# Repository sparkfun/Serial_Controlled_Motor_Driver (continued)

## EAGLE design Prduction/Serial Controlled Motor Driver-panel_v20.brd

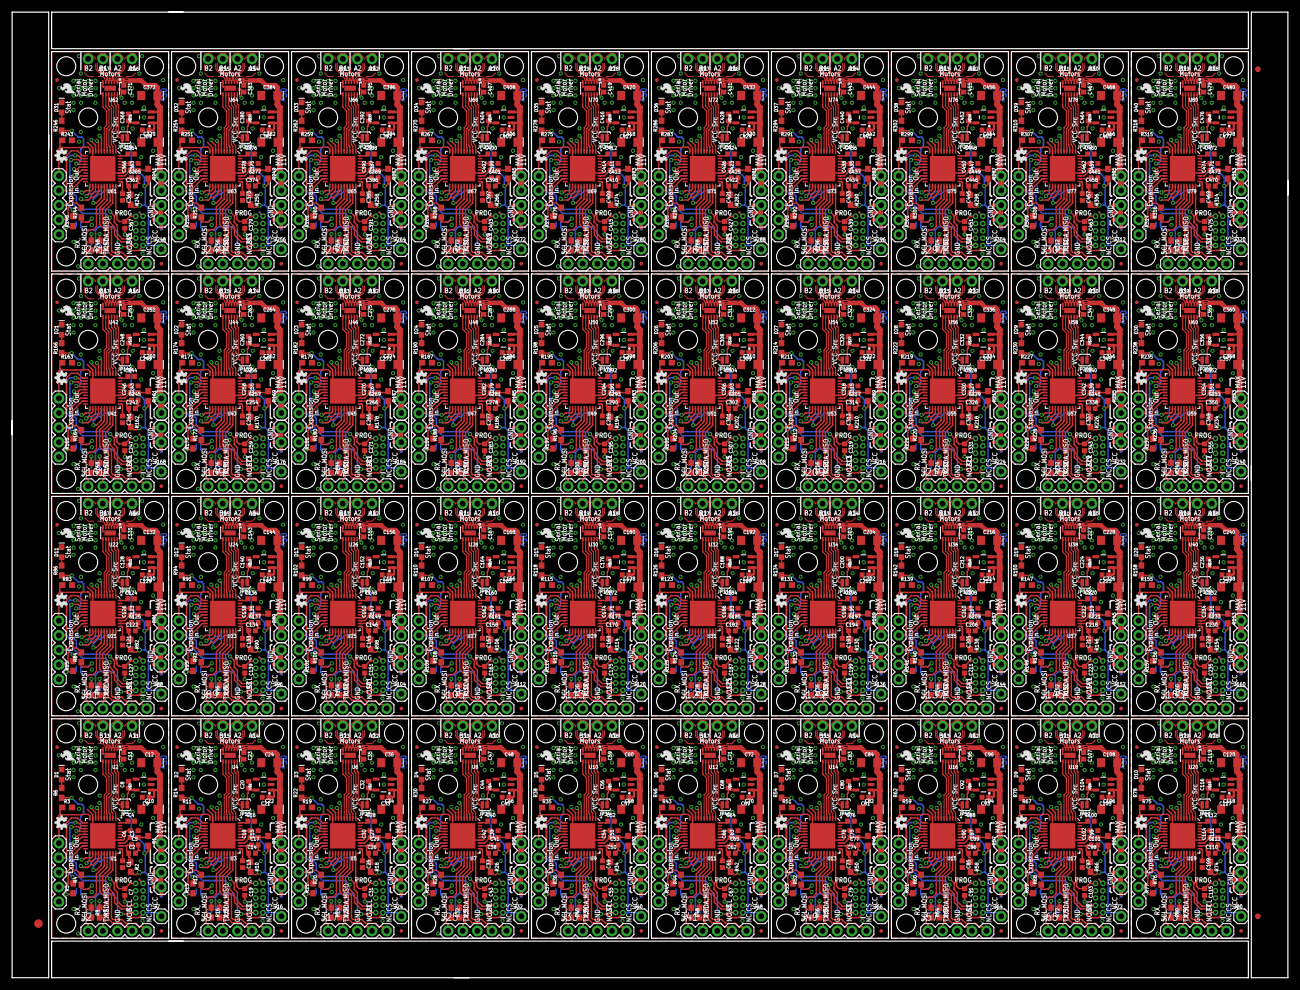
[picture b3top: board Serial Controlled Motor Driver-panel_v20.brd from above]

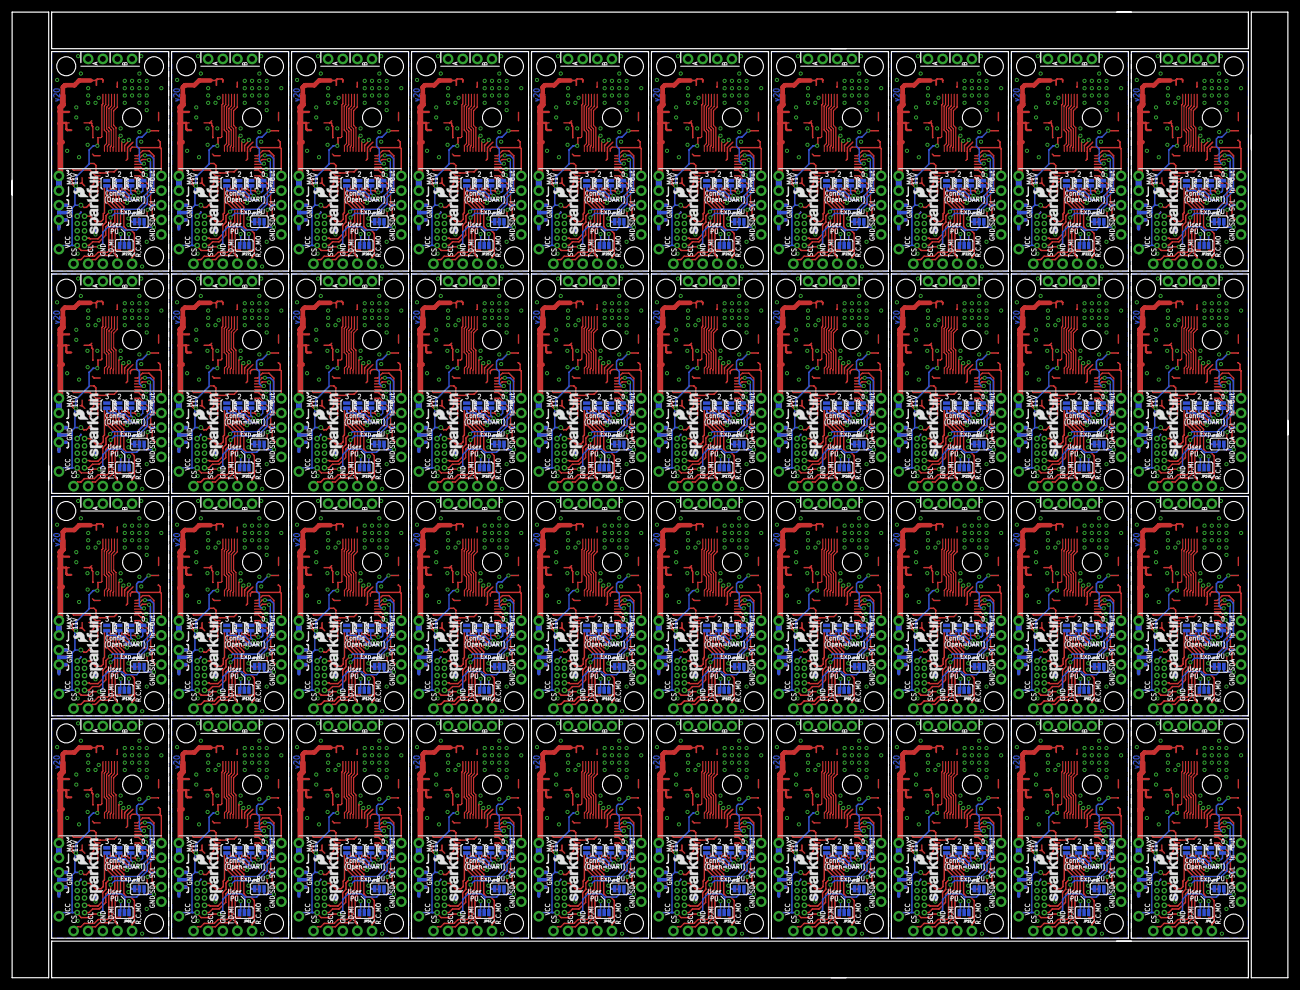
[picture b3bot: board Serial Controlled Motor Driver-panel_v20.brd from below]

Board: 2 copper layers, 221.5 x 167.6 mm, 1923 parts (280 on the bottom side), 1520 nets.

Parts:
C1, C2, C3, C4, C8, C9, C13, C14, C15, C16, C20, C21, C25, C26, C27, C28, C32, C33, C37, C38, C39, C40, C44, C45, C49, C50, C51, C52, C56, C57, C61, C62, C63, C64, C68, C69, C73, C74, C75, C76, C80, C81, C85, C86, C87, C88, C92, C93, C97, C98, C99, C100, C104, C105, C109, C110, C111, C112, C116, C117, C121, C122, C123, C124, C128, C129, C133, C134, C135, C136, C140, C141, C145, C146, C147, C148, C152, C153, C157, C158, C159, C160, C164, C165, C169, C170, C171, C172, C176, C177, C181, C182, C183, C184, C188, C189, C193, C194, C195, C196, C200, C201, C205, C206, C207, C208, C212, C213, C217, C218, C219, C220, C224, C225, C229, C230, C231, C232, C236, C237, C241, C242, C243, C244, C248, C249, C253, C254, C255, C256, C260, C261, C265, C266, C267, C268, C272, C273, C277, C278, C279, C280, C284, C285, C289, C290, C291, C292, C296, C297, C301, C302, C303, C304, C308, C309, C313, C314, C315, C316, C320, C321, C325, C326, C327, C328, C332, C333, C337, C338, C339, C340, C344, C345, C349, C350, C351, C352, C356, C357, C361, C362, C363, C364, C368, C369, C373, C374, C375, C376, C380, C381, C385, C386, C387, C388, C392, C393, C397, C398, C399, C400, C404, C405, C409, C410, C411, C412, C416, C417, C421, C422, C423, C424, C428, C429, C433, C434, C435, C436, C440, C441, C445, C446, C447, C448, C452, C453, C457, C458, C459, C460, C464, C465, C469, C470, C471, C472, C476, C477: 1.0uF; 0402
C5, C6, C7, C11, C17, C18, C19, C23, C29, C30, C31, C35, C41, C42, C43, C47, C53, C54, C55, C59, C65, C66, C67, C71, C77, C78, C79, C83, C89, C90, C91, C95, C101, C102, C103, C107, C113, C114, C115, C119, C125, C126, C127, C131, C137, C138, C139, C143, C149, C150, C151, C155, C161, C162, C163, C167, C173, C174, C175, C179, C185, C186, C187, C191, C197, C198, C199, C203, C209, C210, C211, C215, C221, C222, C223, C227, C233, C234, C235, C239, C245, C246, C247, C251, C257, C258, C259, C263, C269, C270, C271, C275, C281, C282, C283, C287, C293, C294, C295, C299, C305, C306, C307, C311, C317, C318, C319, C323, C329, C330, C331, C335, C341, C342, C343, C347, C353, C354, C355, C359, C365, C366, C367, C371, C377, C378, C379, C383, C389, C390, C391, C395, C401, C402, C403, C407, C413, C414, C415, C419, C425, C426, C427, C431, C437, C438, C439, C443, C449, C450, C451, C455, C461, C462, C463, C467, C473, C474, C475, C479: 0.1uF; 0402
C10, C12, C22, C24, C34, C36, C46, C48, C58, C60, C70, C72, C82, C84, C94, C96, C106, C108, C118, C120, C130, C132, C142, C144, C154, C156, C166, C168, C178, C180, C190, C192, C202, C204, C214, C216, C226, C228, C238, C240, C250, C252, C262, C264, C274, C276, C286, C288, C298, C300, C310, C312, C322, C324, C334, C336, C346, C348, C358, C360, C370, C372, C382, C384, C394, C396, C406, C408, C418, C420, C430, C432, C442, C444, C454, C456, C466, C468, C478, C480: 10uF; EIA3216
D1, D2, D3, D4, D5, D6, D7, D8, D9, D10, D11, D12, D13, D14, D15, D16, D17, D18, D19, D20, D21, D22, D23, D24, D25, D26, D27, D28, D29, D30, D31, D32, D33, D34, D35, D36, D37, D38, D39, D40: RED; LED-0603
E$1: FIDUCIAL-1.5X3
E$5, E$6: FIDUCIAL-1X2
FD1, FD2, FD3, FD4, FD5, FD6, FD7, FD8, FD9, FD10, FD11, FD12, FD13, FD14, FD15, FD16, FD17, FD18, FD19, FD20, FD21, FD22, FD23, FD24, FD25, FD26, FD27, FD28, FD29, FD30, FD31, FD32, FD33, FD34, FD35, FD36, FD37, FD38, FD39, FD40, FD41, FD42, FD43, FD44, FD45, FD46, FD47, FD48, FD49, FD50, FD51, FD52, FD53, FD54, FD55, FD56, FD57, FD58, FD59, FD60, FD61, FD62, FD63, FD64, FD65, FD66, FD67, FD68, FD69, FD70, FD71, FD72, FD73, FD74, FD75, FD76, FD77, FD78, FD79, FD80: FIDUCIALUFIDUCIAL; MICRO-FIDUCIAL
H1, H2, H3, H4, H5, H6, H7, H8, H9, H10, H11, H12, H13, H14, H15, H16, H17, H18, H19, H20, H21, H22, H23, H24, H25, H26, H27, H28, H29, H30, H31, H32, H33, H34, H35, H36, H37, H38, H39, H40, H41, H42, H43, H44, H45, H46, H47, H48, H49, H50, H51, H52, H53, H54, H55, H56, H57, H58, H59, H60, H61, H62, H63, H64, H65, H66, H67, H68, H69, H70, H71, H72, H73, H74, H75, H76, H77, H78, H79, H80, H81, H82, H83, H84, H85, H86, H87, H88, H89, H90, H91, H92, H93, H94, H95, H96, H97, H98, H99, H100, H101, H102, H103, H104, H105, H106, H107, H108, H109, H110, H111, H112, H113, H114, H115, H116, H117, H118, H119, H120, H121, H122, H123, H124, H125, H126, H127, H128, H129, H130, H131, H132, H133, H134, H135, H136, H137, H138, H139, H140, H141, H142, H143, H144, H145, H146, H147, H148, H149, H150, H151, H152, H153, H154, H155, H156, H157, H158, H159, H160: STAND-OFF
J1, J3, J14, J15, J22, J23, J30, J31, J38, J39, J46, J47, J54, J55, J62, J63, J70, J71, J78, J79, J86, J87, J94, J95, J102, J103, J110, J111, J118, J119, J126, J127, J134, J135, J142, J143, J150, J151, J158, J159, J166, J167, J174, J175, J182, J183, J190, J191, J198, J199, J206, J207, J214, J215, J222, J223, J230, J231, J238, J239, J246, J247, J254, J255, J262, J263, J270, J271, J278, J279, J286, J287, J294, J295, J302, J303, J310, J311, J318, J319: DNP; 1X02_NO_SILK
J2, J4, J9, J10, J17, J18, J25, J26, J33, J34, J41, J42, J49, J50, J57, J58, J65, J66, J73, J74, J81, J82, J89, J90, J97, J98, J105, J106, J113, J114, J121, J122, J129, J130, J137, J138, J145, J146, J153, J154, J161, J162, J169, J170, J177, J178, J185, J186, J193, J194, J201, J202, J209, J210, J217, J218, J225, J226, J233, J234, J241, J242, J249, J250, J257, J258, J265, J266, J273, J274, J281, J282, J289, J290, J297, J298, J305, J306, J313, J314: DNP; 1X05
J5, J6, J11, J12, J19, J20, J27, J28, J35, J36, J43, J44, J51, J52, J59, J60, J67, J68, J75, J76, J83, J84, J91, J92, J99, J100, J107, J108, J115, J116, J123, J124, J131, J132, J139, J140, J147, J148, J155, J156, J163, J164, J171, J172, J179, J180, J187, J188, J195, J196, J203, J204, J211, J212, J219, J220, J227, J228, J235, J236, J243, J244, J251, J252, J259, J260, J267, J268, J275, J276, J283, J284, J291, J292, J299, J300, J307, J308, J315, J316: DNP; 1X02@1
J7, J16, J24, J32, J40, J48, J56, J64, J72, J80, J88, J96, J104, J112, J120, J128, J136, J144, J152, J160, J168, J176, J184, J192, J200, J208, J216, J224, J232, J240, J248, J256, J264, J272, J280, J288, J296, J304, J312, J320: DNP; 1X01
J8, J13, J21, J29, J37, J45, J53, J61, J69, J77, J85, J93, J101, J109, J117, J125, J133, J141, J149, J157, J165, J173, J181, J189, J197, J205, J213, J221, J229, J237, J245, J253, J261, J269, J277, J285, J293, J301, J309, J317: CORTEX_DEBUGPTH; 2X5-PTH-1.27MM
JP1, JP2, JP3, JP4, JP8, JP9, JP10, JP11, JP15, JP16, JP17, JP18, JP22, JP23, JP24, JP25, JP29, JP30, JP31, JP32, JP36, JP37, JP38, JP39, JP43, JP44, JP45, JP46, JP50, JP51, JP52, JP53, JP57, JP58, JP59, JP60, JP64, JP65, JP66, JP67, JP71, JP72, JP73, JP74, JP78, JP79, JP80, JP81, JP85, JP86, JP87, JP88, JP92, JP93, JP94, JP95, JP99, JP100, JP101, JP102, JP106, JP107, JP108, JP109, JP113, JP114, JP115, JP116, JP120, JP121, JP122, JP123, JP127, JP128, JP129, JP130, JP134, JP135, JP136, JP137, JP141, JP142, JP143, JP144, JP148, JP149, JP150, JP151, JP155, JP156, JP157, JP158, JP162, JP163, JP164, JP165, JP169, JP170, JP171, JP172, JP176, JP177, JP178, JP179, JP183, JP184, JP185, JP186, JP190, JP191, JP192, JP193, JP197, JP198, JP199, JP200, JP204, JP205, JP206, JP207, JP211, JP212, JP213, JP214, JP218, JP219, JP220, JP221, JP225, JP226, JP227, JP228, JP232, JP233, JP234, JP235, JP239, JP240, JP241, JP242, JP246, JP247, JP248, JP249, JP253, JP254, JP255, JP256, JP260, JP261, JP262, JP263, JP267, JP268, JP269, JP270, JP274, JP275, JP276, JP277: JUMPER-PAD-2; PAD-JUMPER-2-NO_YES_SILK
JP5, JP13, JP20, JP27, JP34, JP41, JP48, JP55, JP62, JP69, JP76, JP83, JP90, JP97, JP104, JP111, JP118, JP125, JP132, JP139, JP146, JP153, JP160, JP167, JP174, JP181, JP188, JP195, JP202, JP209, JP216, JP223, JP230, JP237, JP244, JP251, JP258, JP265, JP272, JP279: JUMPER-PAD-2; PAD-JUMPER-2-NC_BY_PASTE_YES_SILK
JP6, JP7, JP12, JP14, JP19, JP21, JP26, JP28, JP33, JP35, JP40, JP42, JP47, JP49, JP54, JP56, JP61, JP63, JP68, JP70, JP75, JP77, JP82, JP84, JP89, JP91, JP96, JP98, JP103, JP105, JP110, JP112, JP117, JP119, JP124, JP126, JP131, JP133, JP138, JP140, JP145, JP147, JP152, JP154, JP159, JP161, JP166, JP168, JP173, JP175, JP180, JP182, JP187, JP189, JP194, JP196, JP201, JP203, JP208, JP210, JP215, JP217, JP222, JP224, JP229, JP231, JP236, JP238, JP243, JP245, JP250, JP252, JP257, JP259, JP264, JP266, JP271, JP273, JP278, JP280: JUMPER-PAD-3-NOYES_SILK; PAD-JUMPER-3-NO_YES_SILK
LOGO1, LOGO4, LOGO7, LOGO10, LOGO13, LOGO16, LOGO19, LOGO22, LOGO25, LOGO28, LOGO31, LOGO34, LOGO37, LOGO40, LOGO43, LOGO46, LOGO49, LOGO52, LOGO55, LOGO58, LOGO61, LOGO64, LOGO67, LOGO70, LOGO73, LOGO76, LOGO79, LOGO82, LOGO85, LOGO88, LOGO91, LOGO94, LOGO97, LOGO100, LOGO103, LOGO106, LOGO109, LOGO112, LOGO115, LOGO118: SFE_LOGO_FLAME.1_INCH; SFE_LOGO_FLAME_.1
LOGO2, LOGO5, LOGO8, LOGO11, LOGO14, LOGO17, LOGO20, LOGO23, LOGO26, LOGO29, LOGO32, LOGO35, LOGO38, LOGO41, LOGO44, LOGO47, LOGO50, LOGO53, LOGO56, LOGO59, LOGO62, LOGO65, LOGO68, LOGO71, LOGO74, LOGO77, LOGO80, LOGO83, LOGO86, LOGO89, LOGO92, LOGO95, LOGO98, LOGO101, LOGO104, LOGO107, LOGO110, LOGO113, LOGO116, LOGO119: OSHW-LOGOMINI; OSHW-LOGO-MINI
LOGO3, LOGO6, LOGO9, LOGO12, LOGO15, LOGO18, LOGO21, LOGO24, LOGO27, LOGO30, LOGO33, LOGO36, LOGO39, LOGO42, LOGO45, LOGO48, LOGO51, LOGO54, LOGO57, LOGO60, LOGO63, LOGO66, LOGO69, LOGO72, LOGO75, LOGO78, LOGO81, LOGO84, LOGO87, LOGO90, LOGO93, LOGO96, LOGO99, LOGO102, LOGO105, LOGO108, LOGO111, LOGO114, LOGO117, LOGO120: SFE_LOGO_NAME_FLAME.1_INCH; SFE_LOGO_NAME_FLAME_.1
R1, R2, R9, R10, R17, R18, R25, R26, R33, R34, R41, R42, R49, R50, R57, R58, R65, R66, R73, R74, R81, R82, R89, R90, R97, R98, R105, R106, R113, R114, R121, R122, R129, R130, R137, R138, R145, R146, R153, R154, R161, R162, R169, R170, R177, R178, R185, R186, R193, R194, R201, R202, R209, R210, R217, R218, R225, R226, R233, R234, R241, R242, R249, R250, R257, R258, R265, R266, R273, R274, R281, R282, R289, R290, R297, R298, R305, R306, R313, R314: 1; 0603
R3, R4, R5, R7, R8, R11, R12, R13, R15, R16, R19, R20, R21, R23, R24, R27, R28, R29, R31, R32, R35, R36, R37, R39, R40, R43, R44, R45, R47, R48, R51, R52, R53, R55, R56, R59, R60, R61, R63, R64, R67, R68, R69, R71, R72, R75, R76, R77, R79, R80, R83, R84, R85, R87, R88, R91, R92, R93, R95, R96, R99, R100, R101, R103, R104, R107, R108, R109, R111, R112, R115, R116, R117, R119, R120, R123, R124, R125, R127, R128, R131, R132, R133, R135, R136, R139, R140, R141, R143, R144, R147, R148, R149, R151, R152, R155, R156, R157, R159, R160, R163, R164, R165, R167, R168, R171, R172, R173, R175, R176, R179, R180, R181, R183, R184, R187, R188, R189, R191, R192, R195, R196, R197, R199, R200, R203, R204, R205, R207, R208, R211, R212, R213, R215, R216, R219, R220, R221, R223, R224, R227, R228, R229, R231, R232, R235, R236, R237, R239, R240, R243, R244, R245, R247, R248, R251, R252, R253, R255, R256, R259, R260, R261, R263, R264, R267, R268, R269, R271, R272, R275, R276, R277, R279, R280, R283, R284, R285, R287, R288, R291, R292, R293, R295, R296, R299, R300, R301, R303, R304, R307, R308, R309, R311, R312, R315, R316, R317, R319, R320: 4.7k; 0603
R6, R14, R22, R30, R38, R46, R54, R62, R70, R78, R86, R94, R102, R110, R118, R126, R134, R142, R150, R158, R166, R174, R182, R190, R198, R206, R214, R222, R230, R238, R246, R254, R262, R270, R278, R286, R294, R302, R310, R318: 470; 0603
U1, U3, U5, U7, U9, U11, U13, U15, U17, U19, U21, U23, U25, U27, U29, U31, U33, U35, U37, U39, U41, U43, U45, U47, U49, U51, U53, U55, U57, U59, U61, U63, U65, U67, U69, U71, U73, U75, U77, U79: CY8C4245LQI-483; QFN-40
U2, U4, U6, U8, U10, U12, U14, U16, U18, U20, U22, U24, U26, U28, U30, U32, U34, U36, U38, U40, U42, U44, U46, U48, U50, U52, U54, U56, U58, U60, U62, U64, U66, U68, U70, U72, U74, U76, U78, U80: DRV8835; WSON-12
U$1, U$2, U$3, U$4, U$5, U$6, U$7, U$8, U$9, U$10, U$11, U$12, U$13, U$14, U$15, U$16, U$17, U$18, U$19, U$20, U$21, U$22, U$23, U$24, U$25, U$26, U$27, U$28, U$29, U$30, U$31, U$32, U$33, U$34, U$35, U$36, U$37, U$38, U$39, U$40: SPX3819M5_3_3; SOT-23-5-VREG

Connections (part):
!RESET: C7.1, J8.10, U1.30
!RESET1: C19.1, J13.10, U3.30
!RESET2: C31.1, J21.10, U5.30
!RESET3: C43.1, J29.10, U7.30
!RESET4: C55.1, J37.10, U9.30
!RESET5: C67.1, J45.10, U11.30
!RESET6: C79.1, J53.10, U13.30
!RESET7: C91.1, J61.10, U15.30
!RESET8: C103.1, J69.10, U17.30
!RESET9: C115.1, J77.10, U19.30
!RESET10: C127.1, J85.10, U21.30
!RESET11: C139.1, J93.10, U23.30
!RESET12: C151.1, J101.10, U25.30
!RESET13: C163.1, J109.10, U27.30
!RESET14: C175.1, J117.10, U29.30
!RESET15: C187.1, J125.10, U31.30
!RESET16: C199.1, J133.10, U33.30
!RESET17: C211.1, J141.10, U35.30
!RESET18: C223.1, J149.10, U37.30
!RESET19: C235.1, J157.10, U39.30
!RESET20: C247.1, J165.10, U41.30
!RESET21: C259.1, J173.10, U43.30
!RESET22: C271.1, J181.10, U45.30
!RESET23: C283.1, J189.10, U47.30
!RESET24: C295.1, J197.10, U49.30
!RESET25: C307.1, J205.10, U51.30
!RESET26: C319.1, J213.10, U53.30
!RESET27: C331.1, J221.10, U55.30
!RESET28: C343.1, J229.10, U57.30
!RESET29: C355.1, J237.10, U59.30
!RESET30: C367.1, J245.10, U61.30
!RESET31: C379.1, J253.10, U63.30
!RESET32: C391.1, J261.10, U65.30
!RESET33: C403.1, J269.10, U67.30
!RESET34: C415.1, J277.10, U69.30
!RESET35: C427.1, J285.10, U71.30
!RESET36: C439.1, J293.10, U73.30
!RESET37: C451.1, J301.10, U75.30
!RESET38: C463.1, J309.10, U77.30
!RESET39: C475.1, J317.10, U79.30
AOUT1: J1.1, U2.2
AOUT2: J1.2, U2.3
AOUT3: J14.1, U4.2
AOUT4: J14.2, U4.3
AOUT5: J22.1, U6.2
AOUT6: J22.2, U6.3
AOUT7: J30.1, U8.2
AOUT8: J30.2, U8.3
AOUT9: J38.1, U10.2
AOUT10: J38.2, U10.3
AOUT11: J46.1, U12.2
AOUT12: J46.2, U12.3
AOUT13: J54.1, U14.2
AOUT14: J54.2, U14.3
AOUT15: J62.1, U16.2
AOUT16: J62.2, U16.3
AOUT17: J70.1, U18.2
AOUT18: J70.2, U18.3
AOUT19: J78.1, U20.2
AOUT20: J78.2, U20.3
AOUT21: J86.1, U22.2
AOUT22: J86.2, U22.3
AOUT23: J94.1, U24.2
AOUT24: J94.2, U24.3
AOUT25: J102.1, U26.2
AOUT26: J102.2, U26.3
AOUT27: J110.1, U28.2
AOUT28: J110.2, U28.3
AOUT29: J118.1, U30.2
AOUT30: J118.2, U30.3
AOUT31: J126.1, U32.2
AOUT32: J126.2, U32.3
AOUT33: J134.1, U34.2
AOUT34: J134.2, U34.3
AOUT35: J142.1, U36.2
AOUT36: J142.2, U36.3
AOUT37: J150.1, U38.2
AOUT38: J150.2, U38.3
AOUT39: J158.1, U40.2
AOUT40: J158.2, U40.3
AOUT41: J166.1, U42.2
AOUT42: J166.2, U42.3
AOUT43: J174.1, U44.2
AOUT44: J174.2, U44.3
AOUT45: J182.1, U46.2
AOUT46: J182.2, U46.3
AOUT47: J190.1, U48.2
AOUT48: J190.2, U48.3
AOUT49: J198.1, U50.2
AOUT50: J198.2, U50.3
AOUT51: J206.1, U52.2
AOUT52: J206.2, U52.3
AOUT53: J214.1, U54.2
AOUT54: J214.2, U54.3
AOUT55: J222.1, U56.2
AOUT56: J222.2, U56.3
AOUT57: J230.1, U58.2
AOUT58: J230.2, U58.3
AOUT59: J238.1, U60.2
AOUT60: J238.2, U60.3
AOUT61: J246.1, U62.2
AOUT62: J246.2, U62.3
AOUT63: J254.1, U64.2
AOUT64: J254.2, U64.3
AOUT65: J262.1, U66.2
AOUT66: J262.2, U66.3
AOUT67: J270.1, U68.2
AOUT68: J270.2, U68.3
AOUT69: J278.1, U70.2
AOUT70: J278.2, U70.3
AOUT71: J286.1, U72.2
AOUT72: J286.2, U72.3
AOUT73: J294.1, U74.2
AOUT74: J294.2, U74.3
AOUT75: J302.1, U76.2
AOUT76: J302.2, U76.3
AOUT77: J310.1, U78.2
AOUT78: J310.2, U78.3
AOUT79: J318.1, U80.2
AOUT80: J318.2, U80.3
BOUT1: J3.1, U2.4
BOUT2: J3.2, U2.5
BOUT3: J15.1, U4.4
BOUT4: J15.2, U4.5
BOUT5: J23.1, U6.4
BOUT6: J23.2, U6.5
BOUT7: J31.1, U8.4
BOUT8: J31.2, U8.5
BOUT9: J39.1, U10.4
BOUT10: J39.2, U10.5
BOUT11: J47.1, U12.4
BOUT12: J47.2, U12.5
BOUT13: J55.1, U14.4
BOUT14: J55.2, U14.5
BOUT15: J63.1, U16.4
BOUT16: J63.2, U16.5
BOUT17: J71.1, U18.4
BOUT18: J71.2, U18.5
BOUT19: J79.1, U20.4
BOUT20: J79.2, U20.5
BOUT21: J87.1, U22.4
BOUT22: J87.2, U22.5
BOUT23: J95.1, U24.4
BOUT24: J95.2, U24.5
BOUT25: J103.1, U26.4
BOUT26: J103.2, U26.5
BOUT27: J111.1, U28.4
BOUT28: J111.2, U28.5
BOUT29: J119.1, U30.4
BOUT30: J119.2, U30.5
BOUT31: J127.1, U32.4
BOUT32: J127.2, U32.5
BOUT33: J135.1, U34.4
BOUT34: J135.2, U34.5
BOUT35: J143.1, U36.4
BOUT36: J143.2, U36.5
BOUT37: J151.1, U38.4
BOUT38: J151.2, U38.5
BOUT39: J159.1, U40.4
BOUT40: J159.2, U40.5
BOUT41: J167.1, U42.4
BOUT42: J167.2, U42.5
BOUT43: J175.1, U44.4
BOUT44: J175.2, U44.5
BOUT45: J183.1, U46.4
BOUT46: J183.2, U46.5
BOUT47: J191.1, U48.4
BOUT48: J191.2, U48.5
BOUT49: J199.1, U50.4
BOUT50: J199.2, U50.5
BOUT51: J207.1, U52.4
BOUT52: J207.2, U52.5
BOUT53: J215.1, U54.4
BOUT54: J215.2, U54.5
BOUT55: J223.1, U56.4
BOUT56: J223.2, U56.5
BOUT57: J231.1, U58.4
BOUT58: J231.2, U58.5
BOUT59: J239.1, U60.4
BOUT60: J239.2, U60.5
BOUT61: J247.1, U62.4
BOUT62: J247.2, U62.5
BOUT63: J255.1, U64.4
BOUT64: J255.2, U64.5
BOUT65: J263.1, U66.4
BOUT66: J263.2, U66.5
BOUT67: J271.1, U68.4
BOUT68: J271.2, U68.5
BOUT69: J279.1, U70.4
BOUT70: J279.2, U70.5
BOUT71: J287.1, U72.4
BOUT72: J287.2, U72.5
BOUT73: J295.1, U74.4
BOUT74: J295.2, U74.5
BOUT75: J303.1, U76.4
BOUT76: J303.2, U76.5
BOUT77: J311.1, U78.4
BOUT78: J311.2, U78.5
BOUT79: J319.1, U80.4
BOUT80: J319.2, U80.5
CLK_IN: J2.4, U1.28
CLK_IN1: J9.4, U3.28
CLK_IN2: J17.4, U5.28
CLK_IN3: J25.4, U7.28
CLK_IN4: J33.4, U9.28
CLK_IN5: J41.4, U11.28
CLK_IN6: J49.4, U13.28
CLK_IN7: J57.4, U15.28
CLK_IN8: J65.4, U17.28
CLK_IN9: J73.4, U19.28
CLK_IN10: J81.4, U21.28
CLK_IN11: J89.4, U23.28
CLK_IN12: J97.4, U25.28
CLK_IN13: J105.4, U27.28
CLK_IN14: J113.4, U29.28
CLK_IN15: J121.4, U31.28
CLK_IN16: J129.4, U33.28
CLK_IN17: J137.4, U35.28
CLK_IN18: J145.4, U37.28
CLK_IN19: J153.4, U39.28
CLK_IN20: J161.4, U41.28
CLK_IN21: J169.4, U43.28
CLK_IN22: J177.4, U45.28
CLK_IN23: J185.4, U47.28
CLK_IN24: J193.4, U49.28
CLK_IN25: J201.4, U51.28
CLK_IN26: J209.4, U53.28
CLK_IN27: J217.4, U55.28
CLK_IN28: J225.4, U57.28
CLK_IN29: J233.4, U59.28
CLK_IN30: J241.4, U61.28
CLK_IN31: J249.4, U63.28
CLK_IN32: J257.4, U65.28
CLK_IN33: J265.4, U67.28
CLK_IN34: J273.4, U69.28
CLK_IN35: J281.4, U71.28
CLK_IN36: J289.4, U73.28
CLK_IN37: J297.4, U75.28
CLK_IN38: J305.4, U77.28
CLK_IN39: J313.4, U79.28
CONFIG_IN: J4.4, U1.11
CONFIG_IN1: J10.4, U3.11
CONFIG_IN2: J18.4, U5.11
CONFIG_IN3: J26.4, U7.11
CONFIG_IN4: J34.4, U9.11
CONFIG_IN5: J42.4, U11.11
CONFIG_IN6: J50.4, U13.11
CONFIG_IN7: J58.4, U15.11
CONFIG_IN8: J66.4, U17.11
CONFIG_IN9: J74.4, U19.11
CONFIG_IN10: J82.4, U21.11
CONFIG_IN11: J90.4, U23.11
CONFIG_IN12: J98.4, U25.11
CONFIG_IN13: J106.4, U27.11
CONFIG_IN14: J114.4, U29.11
CONFIG_IN15: J122.4, U31.11
CONFIG_IN16: J130.4, U33.11
CONFIG_IN17: J138.4, U35.11
CONFIG_IN18: J146.4, U37.11
CONFIG_IN19: J154.4, U39.11
CONFIG_IN20: J162.4, U41.11
CONFIG_IN21: J170.4, U43.11
CONFIG_IN22: J178.4, U45.11
CONFIG_IN23: J186.4, U47.11
CONFIG_IN24: J194.4, U49.11
CONFIG_IN25: J202.4, U51.11
CONFIG_IN26: J210.4, U53.11
CONFIG_IN27: J218.4, U55.11
CONFIG_IN28: J226.4, U57.11
CONFIG_IN29: J234.4, U59.11
CONFIG_IN30: J242.4, U61.11
CONFIG_IN31: J250.4, U63.11
CONFIG_IN32: J258.4, U65.11
CONFIG_IN33: J266.4, U67.11
CONFIG_IN34: J274.4, U69.11
CONFIG_IN35: J282.4, U71.11
CONFIG_IN36: J290.4, U73.11
CONFIG_IN37: J298.4, U75.11
CONFIG_IN38: J306.4, U77.11
CONFIG_IN39: J314.4, U79.11
CONFIG_OUT: J4.5, R3.1, U1.10
CONFIG_OUT1: J10.5, R11.1, U3.10
CONFIG_OUT2: J18.5, R19.1, U5.10
CONFIG_OUT3: J26.5, R27.1, U7.10
CONFIG_OUT4: J34.5, R35.1, U9.10
CONFIG_OUT5: J42.5, R43.1, U11.10
CONFIG_OUT6: J50.5, R51.1, U13.10
CONFIG_OUT7: J58.5, R59.1, U15.10
CONFIG_OUT8: J66.5, R67.1, U17.10
CONFIG_OUT9: J74.5, R75.1, U19.10
CONFIG_OUT10: J82.5, R83.1, U21.10
CONFIG_OUT11: J90.5, R91.1, U23.10
CONFIG_OUT12: J98.5, R99.1, U25.10
CONFIG_OUT13: J106.5, R107.1, U27.10
CONFIG_OUT14: J114.5, R115.1, U29.10
CONFIG_OUT15: J122.5, R123.1, U31.10
CONFIG_OUT16: J130.5, R131.1, U33.10
CONFIG_OUT17: J138.5, R139.1, U35.10
CONFIG_OUT18: J146.5, R147.1, U37.10
CONFIG_OUT19: J154.5, R155.1, U39.10
CONFIG_OUT20: J162.5, R163.1, U41.10
CONFIG_OUT21: J170.5, R171.1, U43.10
CONFIG_OUT22: J178.5, R179.1, U45.10
CONFIG_OUT23: J186.5, R187.1, U47.10
CONFIG_OUT24: J194.5, R195.1, U49.10
CONFIG_OUT25: J202.5, R203.1, U51.10
CONFIG_OUT26: J210.5, R211.1, U53.10
CONFIG_OUT27: J218.5, R219.1, U55.10
CONFIG_OUT28: J226.5, R227.1, U57.10
CONFIG_OUT29: J234.5, R235.1, U59.10
CONFIG_OUT30: J242.5, R243.1, U61.10
CONFIG_OUT31: J250.5, R251.1, U63.10
CONFIG_OUT32: J258.5, R259.1, U65.10
CONFIG_OUT33: J266.5, R267.1, U67.10
CONFIG_OUT34: J274.5, R275.1, U69.10
CONFIG_OUT35: J282.5, R283.1, U71.10
CONFIG_OUT36: J290.5, R291.1, U73.10
CONFIG_OUT37: J298.5, R299.1, U75.10
CONFIG_OUT38: J306.5, R307.1, U77.10
CONFIG_OUT39: J314.5, R315.1, U79.10
GND: C1.2, C2.2, C3.2, C4.2, C5.2, C6.2, C7.2, C8.2, C9.2, C10.-, C11.2, C12.-, D1.C, J2.3, J4.1, J6.1, J6.2, J8.3, J8.5, J8.7, J8.9, JP1.1, JP2.1, JP3.1, JP4.1, R3.2, U1.9, U1.34, U1.EP, U2.6, U2.PAD, U$3.2
GND1: C13.2, C14.2, C15.2, C16.2, C17.2, C18.2, C19.2, C20.2, C21.2, C22.-, C23.2, C24.-, D2.C, J9.3, J10.1, J12.1, J12.2, J13.3, J13.5, J13.7, J13.9, JP8.1, JP9.1, JP10.1, JP11.1, R11.2, U3.9, U3.34, U3.EP, U4.6, U4.PAD, U$1.2
GND2: C25.2, C26.2, C27.2, C28.2, C29.2, C30.2, C31.2, C32.2, C33.2, C34.-, C35.2, C36.-, D3.C, J17.3, J18.1, J20.1, J20.2, J21.3, J21.5, J21.7, J21.9, JP15.1, JP16.1, JP17.1, JP18.1, R19.2, U5.9, U5.34, U5.EP, U6.6, U6.PAD, U$2.2
GND3: C37.2, C38.2, C39.2, C40.2, C41.2, C42.2, C43.2, C44.2, C45.2, C46.-, C47.2, C48.-, D4.C, J25.3, J26.1, J28.1, J28.2, J29.3, J29.5, J29.7, J29.9, JP22.1, JP23.1, JP24.1, JP25.1, R27.2, U7.9, U7.34, U7.EP, U8.6, U8.PAD, U$4.2
GND4: C49.2, C50.2, C51.2, C52.2, C53.2, C54.2, C55.2, C56.2, C57.2, C58.-, C59.2, C60.-, D5.C, J33.3, J34.1, J36.1, J36.2, J37.3, J37.5, J37.7, J37.9, JP29.1, JP30.1, JP31.1, JP32.1, R35.2, U9.9, U9.34, U9.EP, U10.6, U10.PAD, U$5.2
GND5: C61.2, C62.2, C63.2, C64.2, C65.2, C66.2, C67.2, C68.2, C69.2, C70.-, C71.2, C72.-, D6.C, J41.3, J42.1, J44.1, J44.2, J45.3, J45.5, J45.7, J45.9, JP36.1, JP37.1, JP38.1, JP39.1, R43.2, U11.9, U11.34, U11.EP, U12.6, U12.PAD, U$6.2
GND6: C73.2, C74.2, C75.2, C76.2, C77.2, C78.2, C79.2, C80.2, C81.2, C82.-, C83.2, C84.-, D7.C, J49.3, J50.1, J52.1, J52.2, J53.3, J53.5, J53.7, J53.9, JP43.1, JP44.1, JP45.1, JP46.1, R51.2, U13.9, U13.34, U13.EP, U14.6, U14.PAD, U$7.2
GND7: C85.2, C86.2, C87.2, C88.2, C89.2, C90.2, C91.2, C92.2, C93.2, C94.-, C95.2, C96.-, D8.C, J57.3, J58.1, J60.1, J60.2, J61.3, J61.5, J61.7, J61.9, JP50.1, JP51.1, JP52.1, JP53.1, R59.2, U15.9, U15.34, U15.EP, U16.6, U16.PAD, U$8.2
GND8: C97.2, C98.2, C99.2, C100.2, C101.2, C102.2, C103.2, C104.2, C105.2, C106.-, C107.2, C108.-, D9.C, J65.3, J66.1, J68.1, J68.2, J69.3, J69.5, J69.7, J69.9, JP57.1, JP58.1, JP59.1, JP60.1, R67.2, U17.9, U17.34, U17.EP, U18.6, U18.PAD, U$9.2
GND9: C109.2, C110.2, C111.2, C112.2, C113.2, C114.2, C115.2, C116.2, C117.2, C118.-, C119.2, C120.-, D10.C, J73.3, J74.1, J76.1, J76.2, J77.3, J77.5, J77.7, J77.9, JP64.1, JP65.1, JP66.1, JP67.1, R75.2, U19.9, U19.34, U19.EP, U20.6, U20.PAD, U$10.2
GND10: C121.2, C122.2, C123.2, C124.2, C125.2, C126.2, C127.2, C128.2, C129.2, C130.-, C131.2, C132.-, D11.C, J81.3, J82.1, J84.1, J84.2, J85.3, J85.5, J85.7, J85.9, JP71.1, JP72.1, JP73.1, JP74.1, R83.2, U21.9, U21.34, U21.EP, U22.6, U22.PAD, U$11.2
GND11: C133.2, C134.2, C135.2, C136.2, C137.2, C138.2, C139.2, C140.2, C141.2, C142.-, C143.2, C144.-, D12.C, J89.3, J90.1, J92.1, J92.2, J93.3, J93.5, J93.7, J93.9, JP78.1, JP79.1, JP80.1, JP81.1, R91.2, U23.9, U23.34, U23.EP, U24.6, U24.PAD, U$12.2
GND12: C145.2, C146.2, C147.2, C148.2, C149.2, C150.2, C151.2, C152.2, C153.2, C154.-, C155.2, C156.-, D13.C, J97.3, J98.1, J100.1, J100.2, J101.3, J101.5, J101.7, J101.9, JP85.1, JP86.1, JP87.1, JP88.1, R99.2, U25.9, U25.34, U25.EP, U26.6, U26.PAD, U$13.2
GND13: C157.2, C158.2, C159.2, C160.2, C161.2, C162.2, C163.2, C164.2, C165.2, C166.-, C167.2, C168.-, D14.C, J105.3, J106.1, J108.1, J108.2, J109.3, J109.5, J109.7, J109.9, JP92.1, JP93.1, JP94.1, JP95.1, R107.2, U27.9, U27.34, U27.EP, U28.6, U28.PAD, U$14.2
GND14: C169.2, C170.2, C171.2, C172.2, C173.2, C174.2, C175.2, C176.2, C177.2, C178.-, C179.2, C180.-, D15.C, J113.3, J114.1, J116.1, J116.2, J117.3, J117.5, J117.7, J117.9, JP99.1, JP100.1, JP101.1, JP102.1, R115.2, U29.9, U29.34, U29.EP, U30.6, U30.PAD, U$15.2
GND15: C181.2, C182.2, C183.2, C184.2, C185.2, C186.2, C187.2, C188.2, C189.2, C190.-, C191.2, C192.-, D16.C, J121.3, J122.1, J124.1, J124.2, J125.3, J125.5, J125.7, J125.9, JP106.1, JP107.1, JP108.1, JP109.1, R123.2, U31.9, U31.34, U31.EP, U32.6, U32.PAD, U$16.2
GND16: C193.2, C194.2, C195.2, C196.2, C197.2, C198.2, C199.2, C200.2, C201.2, C202.-, C203.2, C204.-, D17.C, J129.3, J130.1, J132.1, J132.2, J133.3, J133.5, J133.7, J133.9, JP113.1, JP114.1, JP115.1, JP116.1, R131.2, U33.9, U33.34, U33.EP, U34.6, U34.PAD, U$17.2
GND17: C205.2, C206.2, C207.2, C208.2, C209.2, C210.2, C211.2, C212.2, C213.2, C214.-, C215.2, C216.-, D18.C, J137.3, J138.1, J140.1, J140.2, J141.3, J141.5, J141.7, J141.9, JP120.1, JP121.1, JP122.1, JP123.1, R139.2, U35.9, U35.34, U35.EP, U36.6, U36.PAD, U$18.2
GND18: C217.2, C218.2, C219.2, C220.2, C221.2, C222.2, C223.2, C224.2, C225.2, C226.-, C227.2, C228.-, D19.C, J145.3, J146.1, J148.1, J148.2, J149.3, J149.5, J149.7, J149.9, JP127.1, JP128.1, JP129.1, JP130.1, R147.2, U37.9, U37.34, U37.EP, U38.6, U38.PAD, U$19.2
GND19: C229.2, C230.2, C231.2, C232.2, C233.2, C234.2, C235.2, C236.2, C237.2, C238.-, C239.2, C240.-, D20.C, J153.3, J154.1, J156.1, J156.2, J157.3, J157.5, J157.7, J157.9, JP134.1, JP135.1, JP136.1, JP137.1, R155.2, U39.9, U39.34, U39.EP, U40.6, U40.PAD, U$20.2
GND20: C241.2, C242.2, C243.2, C244.2, C245.2, C246.2, C247.2, C248.2, C249.2, C250.-, C251.2, C252.-, D21.C, J161.3, J162.1, J164.1, J164.2, J165.3, J165.5, J165.7, J165.9, JP141.1, JP142.1, JP143.1, JP144.1, R163.2, U41.9, U41.34, U41.EP, U42.6, U42.PAD, U$21.2
GND21: C253.2, C254.2, C255.2, C256.2, C257.2, C258.2, C259.2, C260.2, C261.2, C262.-, C263.2, C264.-, D22.C, J169.3, J170.1, J172.1, J172.2, J173.3, J173.5, J173.7, J173.9, JP148.1, JP149.1, JP150.1, JP151.1, R171.2, U43.9, U43.34, U43.EP, U44.6, U44.PAD, U$22.2
GND22: C265.2, C266.2, C267.2, C268.2, C269.2, C270.2, C271.2, C272.2, C273.2, C274.-, C275.2, C276.-, D23.C, J177.3, J178.1, J180.1, J180.2, J181.3, J181.5, J181.7, J181.9, JP155.1, JP156.1, JP157.1, JP158.1, R179.2, U45.9, U45.34, U45.EP, U46.6, U46.PAD, U$23.2
GND23: C277.2, C278.2, C279.2, C280.2, C281.2, C282.2, C283.2, C284.2, C285.2, C286.-, C287.2, C288.-, D24.C, J185.3, J186.1, J188.1, J188.2, J189.3, J189.5, J189.7, J189.9, JP162.1, JP163.1, JP164.1, JP165.1, R187.2, U47.9, U47.34, U47.EP, U48.6, U48.PAD, U$24.2
GND24: C289.2, C290.2, C291.2, C292.2, C293.2, C294.2, C295.2, C296.2, C297.2, C298.-, C299.2, C300.-, D25.C, J193.3, J194.1, J196.1, J196.2, J197.3, J197.5, J197.7, J197.9, JP169.1, JP170.1, JP171.1, JP172.1, R195.2, U49.9, U49.34, U49.EP, U50.6, U50.PAD, U$25.2
GND25: C301.2, C302.2, C303.2, C304.2, C305.2, C306.2, C307.2, C308.2, C309.2, C310.-, C311.2, C312.-, D26.C, J201.3, J202.1, J204.1, J204.2, J205.3, J205.5, J205.7, J205.9, JP176.1, JP177.1, JP178.1, JP179.1, R203.2, U51.9, U51.34, U51.EP, U52.6, U52.PAD, U$26.2
GND26: C313.2, C314.2, C315.2, C316.2, C317.2, C318.2, C319.2, C320.2, C321.2, C322.-, C323.2, C324.-, D27.C, J209.3, J210.1, J212.1, J212.2, J213.3, J213.5, J213.7, J213.9, JP183.1, JP184.1, JP185.1, JP186.1, R211.2, U53.9, U53.34, U53.EP, U54.6, U54.PAD, U$27.2
GND27: C325.2, C326.2, C327.2, C328.2, C329.2, C330.2, C331.2, C332.2, C333.2, C334.-, C335.2, C336.-, D28.C, J217.3, J218.1, J220.1, J220.2, J221.3, J221.5, J221.7, J221.9, JP190.1, JP191.1, JP192.1, JP193.1, R219.2, U55.9, U55.34, U55.EP, U56.6, U56.PAD, U$28.2
GND28: C337.2, C338.2, C339.2, C340.2, C341.2, C342.2, C343.2, C344.2, C345.2, C346.-, C347.2, C348.-, D29.C, J225.3, J226.1, J228.1, J228.2, J229.3, J229.5, J229.7, J229.9, JP197.1, JP198.1, JP199.1, JP200.1, R227.2, U57.9, U57.34, U57.EP, U58.6, U58.PAD, U$29.2
GND29: C349.2, C350.2, C351.2, C352.2, C353.2, C354.2, C355.2, C356.2, C357.2, C358.-, C359.2, C360.-, D30.C, J233.3, J234.1, J236.1, J236.2, J237.3, J237.5, J237.7, J237.9, JP204.1, JP205.1, JP206.1, JP207.1, R235.2, U59.9, U59.34, U59.EP, U60.6, U60.PAD, U$30.2
GND30: C361.2, C362.2, C363.2, C364.2, C365.2, C366.2, C367.2, C368.2, C369.2, C370.-, C371.2, C372.-, D31.C, J241.3, J242.1, J244.1, J244.2, J245.3, J245.5, J245.7, J245.9, JP211.1, JP212.1, JP213.1, JP214.1, R243.2, U61.9, U61.34, U61.EP, U62.6, U62.PAD, U$31.2
GND31: C373.2, C374.2, C375.2, C376.2, C377.2, C378.2, C379.2, C380.2, C381.2, C382.-, C383.2, C384.-, D32.C, J249.3, J250.1, J252.1, J252.2, J253.3, J253.5, J253.7, J253.9, JP218.1, JP219.1, JP220.1, JP221.1, R251.2, U63.9, U63.34, U63.EP, U64.6, U64.PAD, U$32.2
GND32: C385.2, C386.2, C387.2, C388.2, C389.2, C390.2, C391.2, C392.2, C393.2, C394.-, C395.2, C396.-, D33.C, J257.3, J258.1, J260.1, J260.2, J261.3, J261.5, J261.7, J261.9, JP225.1, JP226.1, JP227.1, JP228.1, R259.2, U65.9, U65.34, U65.EP, U66.6, U66.PAD, U$33.2
GND33: C397.2, C398.2, C399.2, C400.2, C401.2, C402.2, C403.2, C404.2, C405.2, C406.-, C407.2, C408.-, D34.C, J265.3, J266.1, J268.1, J268.2, J269.3, J269.5, J269.7, J269.9, JP232.1, JP233.1, JP234.1, JP235.1, R267.2, U67.9, U67.34, U67.EP, U68.6, U68.PAD, U$34.2
GND34: C409.2, C410.2, C411.2, C412.2, C413.2, C414.2, C415.2, C416.2, C417.2, C418.-, C419.2, C420.-, D35.C, J273.3, J274.1, J276.1, J276.2, J277.3, J277.5, J277.7, J277.9, JP239.1, JP240.1, JP241.1, JP242.1, R275.2, U69.9, U69.34, U69.EP, U70.6, U70.PAD, U$35.2
GND35: C421.2, C422.2, C423.2, C424.2, C425.2, C426.2, C427.2, C428.2, C429.2, C430.-, C431.2, C432.-, D36.C, J281.3, J282.1, J284.1, J284.2, J285.3, J285.5, J285.7, J285.9, JP246.1, JP247.1, JP248.1, JP249.1, R283.2, U71.9, U71.34, U71.EP, U72.6, U72.PAD, U$36.2
GND36: C433.2, C434.2, C435.2, C436.2, C437.2, C438.2, C439.2, C440.2, C441.2, C442.-, C443.2, C444.-, D37.C, J289.3, J290.1, J292.1, J292.2, J293.3, J293.5, J293.7, J293.9, JP253.1, JP254.1, JP255.1, JP256.1, R291.2, U73.9, U73.34, U73.EP, U74.6, U74.PAD, U$37.2
GND37: C445.2, C446.2, C447.2, C448.2, C449.2, C450.2, C451.2, C452.2, C453.2, C454.-, C455.2, C456.-, D38.C, J297.3, J298.1, J300.1, J300.2, J301.3, J301.5, J301.7, J301.9, JP260.1, JP261.1, JP262.1, JP263.1, R299.2, U75.9, U75.34, U75.EP, U76.6, U76.PAD, U$38.2
GND38: C457.2, C458.2, C459.2, C460.2, C461.2, C462.2, C463.2, C464.2, C465.2, C466.-, C467.2, C468.-, D39.C, J305.3, J306.1, J308.1, J308.2, J309.3, J309.5, J309.7, J309.9, JP267.1, JP268.1, JP269.1, JP270.1, R307.2, U77.9, U77.34, U77.EP, U78.6, U78.PAD, U$39.2
GND39: C469.2, C470.2, C471.2, C472.2, C473.2, C474.2, C475.2, C476.2, C477.2, C478.-, C479.2, C480.-, D40.C, J313.3, J314.1, J316.1, J316.2, J317.3, J317.5, J317.7, J317.9, JP274.1, JP275.1, JP276.1, JP277.1, R315.2, U79.9, U79.34, U79.EP, U80.6, U80.PAD, U$40.2
MODEB0: JP4.2, U1.22
MODEB1: JP3.2, U1.23
MODEB2: JP2.2, U1.24
MODEB3: JP1.2, U1.25
MODEB4: JP11.2, U3.22
MODEB5: JP10.2, U3.23
MODEB6: JP9.2, U3.24
MODEB7: JP8.2, U3.25
MODEB8: JP18.2, U5.22
MODEB9: JP17.2, U5.23
MODEB10: JP16.2, U5.24
MODEB11: JP15.2, U5.25
MODEB12: JP25.2, U7.22
MODEB13: JP24.2, U7.23
MODEB14: JP23.2, U7.24
MODEB15: JP22.2, U7.25
MODEB16: JP32.2, U9.22
MODEB17: JP31.2, U9.23
MODEB18: JP30.2, U9.24
MODEB19: JP29.2, U9.25
MODEB20: JP39.2, U11.22
MODEB21: JP38.2, U11.23
MODEB22: JP37.2, U11.24
MODEB23: JP36.2, U11.25
MODEB24: JP46.2, U13.22
MODEB25: JP45.2, U13.23
MODEB26: JP44.2, U13.24
MODEB27: JP43.2, U13.25
MODEB28: JP53.2, U15.22
MODEB29: JP52.2, U15.23
MODEB30: JP51.2, U15.24
MODEB31: JP50.2, U15.25
MODEB32: JP60.2, U17.22
MODEB33: JP59.2, U17.23
MODEB34: JP58.2, U17.24
MODEB35: JP57.2, U17.25
MODEB36: JP67.2, U19.22
MODEB37: JP66.2, U19.23
MODEB38: JP65.2, U19.24
MODEB39: JP64.2, U19.25
MODEB40: JP74.2, U21.22
MODEB41: JP73.2, U21.23
MODEB42: JP72.2, U21.24
MODEB43: JP71.2, U21.25
MODEB44: JP81.2, U23.22
MODEB45: JP80.2, U23.23
MODEB46: JP79.2, U23.24
MODEB47: JP78.2, U23.25
MODEB48: JP88.2, U25.22
MODEB49: JP87.2, U25.23
MODEB50: JP86.2, U25.24
MODEB51: JP85.2, U25.25
MODEB52: JP95.2, U27.22
MODEB53: JP94.2, U27.23
MODEB54: JP93.2, U27.24
MODEB55: JP92.2, U27.25
MODEB56: JP102.2, U29.22
MODEB57: JP101.2, U29.23
MODEB58: JP100.2, U29.24
MODEB59: JP99.2, U29.25
MODEB60: JP109.2, U31.22
MODEB61: JP108.2, U31.23
MODEB62: JP107.2, U31.24
MODEB63: JP106.2, U31.25
MODEB64: JP116.2, U33.22
MODEB65: JP115.2, U33.23
MODEB66: JP114.2, U33.24
MODEB67: JP113.2, U33.25
MODEB68: JP123.2, U35.22
MODEB69: JP122.2, U35.23
MODEB70: JP121.2, U35.24
MODEB71: JP120.2, U35.25
MODEB72: JP130.2, U37.22
MODEB73: JP129.2, U37.23
MODEB74: JP128.2, U37.24
MODEB75: JP127.2, U37.25
MODEB76: JP137.2, U39.22
MODEB77: JP136.2, U39.23
MODEB78: JP135.2, U39.24
MODEB79: JP134.2, U39.25
MODEB80: JP144.2, U41.22
MODEB81: JP143.2, U41.23
MODEB82: JP142.2, U41.24
MODEB83: JP141.2, U41.25
MODEB84: JP151.2, U43.22
MODEB85: JP150.2, U43.23
MODEB86: JP149.2, U43.24
MODEB87: JP148.2, U43.25
MODEB88: JP158.2, U45.22
MODEB89: JP157.2, U45.23
MODEB90: JP156.2, U45.24
MODEB91: JP155.2, U45.25
MODEB92: JP165.2, U47.22
MODEB93: JP164.2, U47.23
MODEB94: JP163.2, U47.24
MODEB95: JP162.2, U47.25
MODEB96: JP172.2, U49.22
MODEB97: JP171.2, U49.23
MODEB98: JP170.2, U49.24
MODEB99: JP169.2, U49.25
MODEB100: JP179.2, U51.22
MODEB101: JP178.2, U51.23
MODEB102: JP177.2, U51.24
MODEB103: JP176.2, U51.25
MODEB104: JP186.2, U53.22
MODEB105: JP185.2, U53.23
MODEB106: JP184.2, U53.24
MODEB107: JP183.2, U53.25
MODEB108: JP193.2, U55.22
MODEB109: JP192.2, U55.23
MODEB110: JP191.2, U55.24
MODEB111: JP190.2, U55.25
MODEB112: JP200.2, U57.22
MODEB113: JP199.2, U57.23
MODEB114: JP198.2, U57.24
MODEB115: JP197.2, U57.25
MODEB116: JP207.2, U59.22
MODEB117: JP206.2, U59.23
MODEB118: JP205.2, U59.24
MODEB119: JP204.2, U59.25
MODEB120: JP214.2, U61.22
MODEB121: JP213.2, U61.23
MODEB122: JP212.2, U61.24
MODEB123: JP211.2, U61.25
MODEB124: JP221.2, U63.22
MODEB125: JP220.2, U63.23
MODEB126: JP219.2, U63.24
MODEB127: JP218.2, U63.25
MODEB128: JP228.2, U65.22
MODEB129: JP227.2, U65.23
MODEB130: JP226.2, U65.24
MODEB131: JP225.2, U65.25
MODEB132: JP235.2, U67.22
MODEB133: JP234.2, U67.23
MODEB134: JP233.2, U67.24
MODEB135: JP232.2, U67.25
MODEB136: JP242.2, U69.22
MODEB137: JP241.2, U69.23
MODEB138: JP240.2, U69.24
MODEB139: JP239.2, U69.25
MODEB140: JP249.2, U71.22
MODEB141: JP248.2, U71.23
MODEB142: JP247.2, U71.24
MODEB143: JP246.2, U71.25
MODEB144: JP256.2, U73.22
MODEB145: JP255.2, U73.23
MODEB146: JP254.2, U73.24
MODEB147: JP253.2, U73.25
MODEB148: JP263.2, U75.22
MODEB149: JP262.2, U75.23
MODEB150: JP261.2, U75.24
MODEB151: JP260.2, U75.25
MODEB152: JP270.2, U77.22
MODEB153: JP269.2, U77.23
MODEB154: JP268.2, U77.24
MODEB155: JP267.2, U77.25
MODEB156: JP277.2, U79.22
MODEB157: JP276.2, U79.23
MODEB158: JP275.2, U79.24
MODEB159: JP274.2, U79.25
unnamed: C1.1, U1.31
unnamed: JP7.1, R4.1
unnamed: C3.1, C6.1, R1.1, U1.33
unnamed: C4.1, U1.40
unnamed: C8.1, JP5.1, U$3.5
unnamed: JP7.3, R5.1
unnamed: C13.1, U3.31
unnamed: C15.1, C18.1, R9.1, U3.33
unnamed: C16.1, U3.40
unnamed: D1.A, R6.2
unnamed: JP6.1, R8.1
unnamed: JP6.3, R7.1
unnamed: D2.A, R14.2
unnamed: JP12.1, R16.1
unnamed: JP12.3, R15.1
unnamed: C20.1, JP13.1, U$1.5
unnamed: JP14.1, R12.1
unnamed: JP14.3, R13.1
unnamed: C25.1, U5.31
unnamed: C27.1, C30.1, R17.1, U5.33
unnamed: C28.1, U5.40
unnamed: D3.A, R22.2
unnamed: JP19.1, R24.1
unnamed: JP19.3, R23.1
unnamed: C32.1, JP20.1, U$2.5
unnamed: JP21.1, R20.1
unnamed: JP21.3, R21.1
unnamed: C37.1, U7.31
unnamed: C39.1, C42.1, R25.1, U7.33
unnamed: C40.1, U7.40
unnamed: D4.A, R30.2
unnamed: JP26.1, R32.1
unnamed: JP26.3, R31.1
unnamed: C44.1, JP27.1, U$4.5
unnamed: JP28.1, R28.1
unnamed: JP28.3, R29.1
unnamed: C49.1, U9.31
unnamed: C51.1, C54.1, R33.1, U9.33
unnamed: C52.1, U9.40
unnamed: D5.A, R38.2
unnamed: JP33.1, R40.1
unnamed: JP33.3, R39.1
unnamed: C56.1, JP34.1, U$5.5
unnamed: JP35.1, R36.1
unnamed: JP35.3, R37.1
unnamed: C61.1, U11.31
unnamed: C63.1, C66.1, R41.1, U11.33
unnamed: C64.1, U11.40
unnamed: D6.A, R46.2
unnamed: JP40.1, R48.1
unnamed: JP40.3, R47.1
unnamed: C68.1, JP41.1, U$6.5
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
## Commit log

2015-03-09 Adding hardware files, README
2016-04-18 added new design
2016-04-20 Sending it home
2016-04-21 Working on checklist
2016-04-22 Finished checklist
2016-06-30 bringing branch up to date with physical hardware v1.5
2016-06-30 Bringing branch up to date with current design work while tracking only necessary PSoC build files
2016-07-06 Added no-driver version for development
2016-07-15 Made non-zero widths and put tags in readme
2016-07-15 Incremented version numbers in eagle files
2016-07-15 Thickened poly lines to 0.001 inch
2016-07-17 Established simple API sketch to run on either Arduino UNO or Teensy 3.2
2016-07-20 Brought 2nd proto up, fixed i2c config bug
2016-07-26 Working on release FW, added status LED, config bit reading, starting to fill out the register map
2016-07-27 Added I2C error checking, saves into register map
2016-08-03 Snapshot of the single driver only code. All IO added, LED behaves well, driver good for driving robots. Expansion port configured to be master, and can take random data from a slave through a junky 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
2016-08-04 got read and write to slave device working, though experiencing a bus lockup when there's no slave at the specified address
2016-08-04 Now supports enumeration of slave devices. During boot, slaves are assigned an address based on when the CONFIG_IN pin goes high. Also did a bit of work on the UNO test appliance.
2016-08-04 removed lock files
2016-08-06 Added self-reboot to slaves that lose sync, added max 16 slaves, debugged
2016-08-09 Fixed proto errors and started final API for arduino
2016-08-11 added test docs
2016-08-11 Added Byron's review suggestions
2016-08-12 Finished review and implemented changes, double checked serial pin functions to match silk
2016-08-16 Paneling of board
    Board Panel reviewed with Marshall.
2016-08-16 Fixed naming
    Fixed naming forgot pcb #
2016-09-26 Added uart parser and documentation
2016-09-27 Implemented arbitrary uart RW and polarity/bridging mux
2016-09-29 Alpha release of firmware. All functions implemented but require testing and debugging.
2016-09-30 moved constants to devRegisters.c from main.c
2016-09-30 Moved excess code from main.c into included files
2016-10-02 Added documentation and condensed UART parsing code
2016-10-02 autosave
2016-10-03 Fixed headers, cleaned up a bit
2016-10-04 Purged examples, writing arduino library
2016-10-12 Major reworking of FW and SW complete. I2C and SPI work through the Arduino library. I2C, SPI, UART, and slave operation works in the FW, very near to as expected.
2016-10-14 Added product info
2016-10-16 added diag, timeout, refined failsafe, wrote diag example
2016-10-17 Created new files, and moved functions, for serial parsers and device register actions
2016-10-18 Enabled write lockouts, rearranged device registers
2016-10-18 Created QC dev release
2016-10-18 switched to DEBUG built fw
2016-10-19 polished functions
2016-10-19 Started datasheet
2016-10-20 working out serial timing
2016-10-20 Reorganized serial. Created handlers for user and expansion bus divider registers, and broke serial init up into smaller parts.
2016-10-20 Beta release of firmware
2016-10-24 worked on documentation
2016-10-25 More documentation changes
2016-10-25 Polished library and getting ready to split into new repo
2016-10-26 Documentation update
2016-10-27 Working on QC test
2016-10-27 Renamed workspace for release
2016-10-27 added some test mode stuff and removed old workspaces. Generated SCMD_FID_04.HEX
2016-10-29 Working on documentation
2016-10-31 Tweaking operation
2016-10-31 Updated documentation
2016-11-02 worked on datasheet
2016-11-02 Drew enumeration diagrams
2016-11-03 Overhauled boot order and reboot operations, added busy bit
2016-11-03 Debugging serial parser
2016-11-04 Added enumeration diagrams to datasheet
2016-11-06 Finalized pin map, moved main FW folder but leaving the original pre-UART prompt addition
2016-11-06 Getting very close to release, tests looking good but failsafe isn't quite there
2016-11-07 Everything is broken
2016-11-08 Built release firmware 06
2016-11-10 Exported PDF datasheet
2016-11-10 Touched up PDF
2016-11-18 Removing .lck file in Production directory
2016-11-18 Adding license, updating readme, updating .git files
2016-11-18 updated readme of software directory and added video test program
2016-11-18 Squashed 'Libraries/Arduino/' content from commit a6f2818
    git-subtree-dir: Libraries/Arduino
    git-subtree-split: a6f281868b108a5d845209acaeb743df012d8111
2016-11-18 Adding subtree info to libraries readme
2017-05-04 Added enable pin at U2.5, readable by status_1 at 0x77, bit 2
2017-06-21 Created FW version 07 which is compatible with the moto_bit and the serial controlled motor driver. FW ID can be read at address 0x00 and the enable pin state at 0x77, bit 2
2017-06-22 bug fix on release
2017-06-22 Updated documentation and config header for moto:bit application. Bit position of 0x77 for reading enable state moved from b2 to b4
2019-12-19 v07b
    - Added SCMD_FW07b.hex
    - SCMD_config.h - Updated FIRMWARE_VERSION from 0x07 to 0x7B
    - Serial.c - Changed TIMEOUTCOUNTLIMIT from 50,000 to 150
